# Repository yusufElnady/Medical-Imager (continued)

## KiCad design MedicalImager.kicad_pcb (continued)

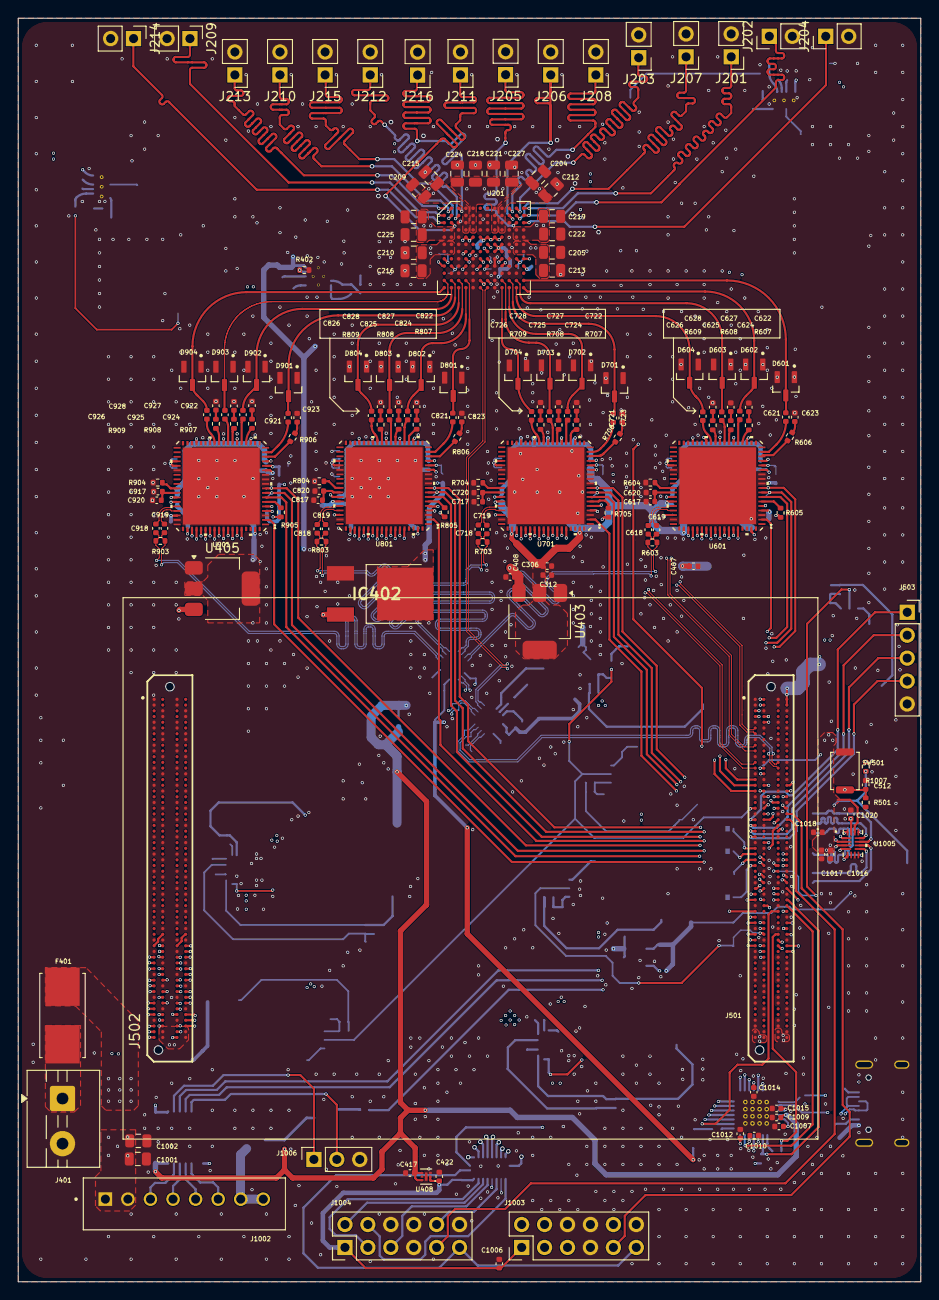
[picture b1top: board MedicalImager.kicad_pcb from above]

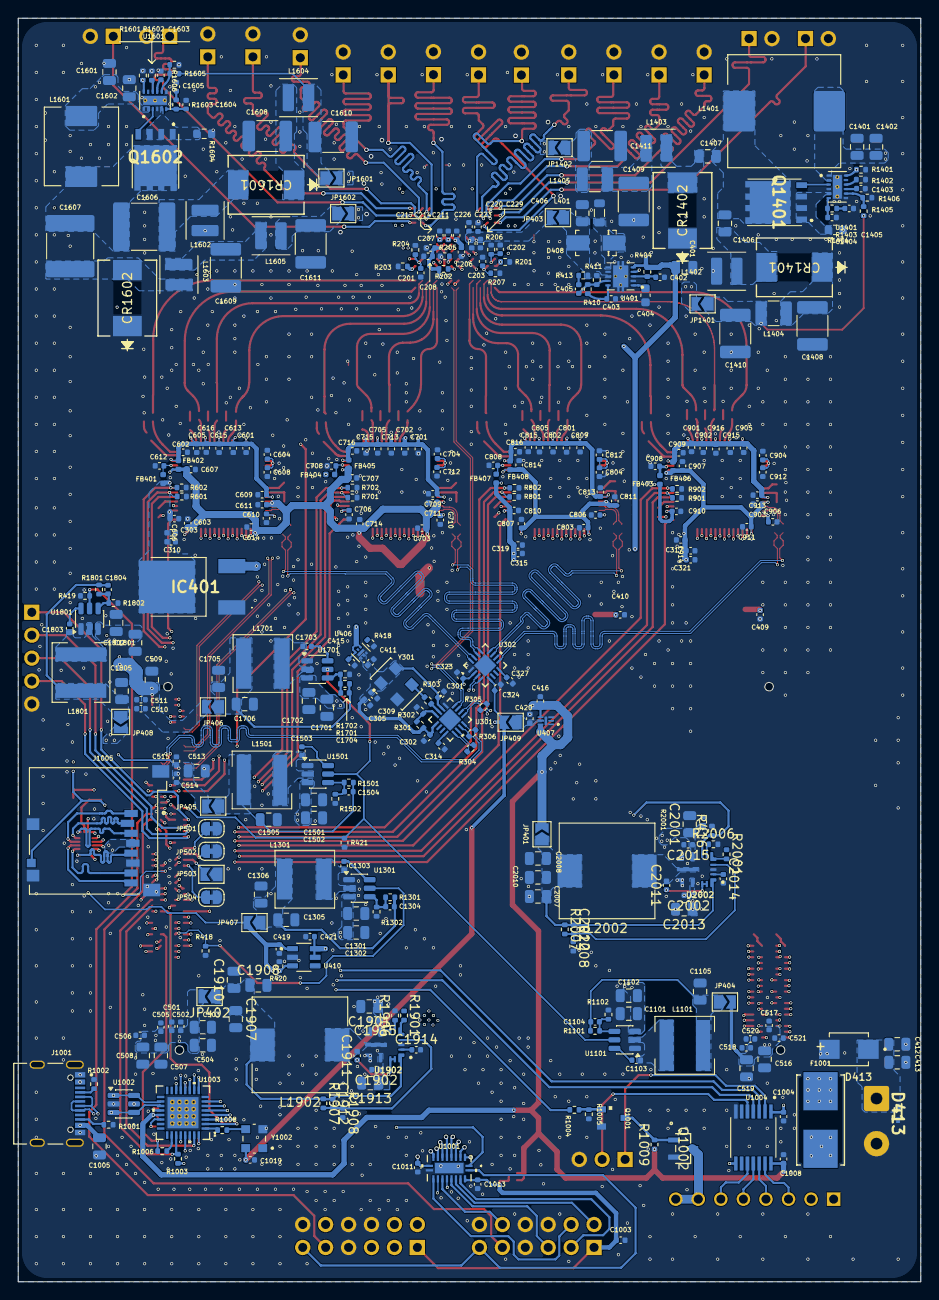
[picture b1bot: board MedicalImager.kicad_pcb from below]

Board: 6 copper layers, 100.0 x 140.0 mm, 519 parts (352 on the bottom side), 394 nets.

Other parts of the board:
D413#2: SMBJ30A; DIOM4336X265N
R418#2: 10K; R_0402_1005Metric
R2001#2: 4K; R_0402_1005Metric

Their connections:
DC_MAIN: R2001#2.1; also elsewhere on the board
DC_MAIN_PRE: D413#2.C; also elsewhere on the board
GND: D413#2.A, R418#2.2; also elsewhere on the board

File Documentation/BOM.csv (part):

Reference;Value;Footprint;Description
C201,C202,C203;1nF;Capacitor_SMD:C_0402_1005Metric;1nF 0402
C204,C205,C209,C210,C212,C213,C215,C216,C218,C219,C221,C222,C224,C225,C227,C228;100nF 200V;Capacitor_SMD:C_0805_2012Metric;100nF 200V 0805
C206,C207,C208,C211,C214,C217,C220,C223,C226,C229,C302,C305,C314,C324,C327,C402,C501,C505,C510,C511,C512,C514,C515,C517,C518,C520,C521,C601,C602,C603,C604,C605,C606,C607,C608,C609,C610,C611,C612,C613,C614,C615,C616,C618,C619,C620,C621,C622,C623,C624,C625,C626,C627,C628,C701,C702,C703,C704,C705,C706,C707,C708,C709,C710,C711,C712,C713,C714,C715,C716,C718,C719,C720,C721,C722,C723,C724,C725,C726,C727,C728,C801,C802,C803,C804,C805,C806,C807,C808,C809,C810,C811,C812,C813,C814,C815,C816,C818,C819,C820,C821,C822,C823,C824,C825,C826,C827,C828,C901,C902,C903,C904,C905,C906,C907,C908,C909,C910,C911,C912,C913,C914,C915,C916,C918,C919,C920,C921,C922,C923,C924,C925,C926,C927,C928,C1004,C1007,C1008,C1009,C1010,C1012,C1017,C1018,C1019,C1020,C1103,C1303,C1403,C1503,C1603,C1703,C1803,C1904,C1906,C2004,C2006;100nF;Capacitor_SMD:C_0402_1005Metric;100nF 0402,100nF 50v 0402
C301,C309,C323;10uF;Capacitor_SMD:C_0402_1005Metric;10uF 0402
C303,C306,C310,C312,C315,C317,C319,C321,C407,C408,C409,C410,C411,C415,C416,C417,C419,C420,C421,C422,C502,C506,C617,C717,C817,C917,C1003,C1006,C1011,C1013,C1016,C1905,C2005;1uF;Capacitor_SMD:C_0402_1005Metric;1uF 0402
C401,C412,C413,C1101,C1102,C1301,C1302,C1401,C1402,C1501,C1502,C1601,C1602,C1701,C1702,C1801,C1802;10uF;Capacitor_SMD:C_0805_2012Metric;10uF 0805 50V,10uF >10v 0805
C403;220nF;Capacitor_SMD:C_0402_1005Metric;220nF 0402
C404;4.7nF;Capacitor_SMD:C_0603_1608Metric;4.7nF 50v 0805
C405;10pF;Capacitor_SMD:C_0402_1005Metric;10pF 0402
C406;22uF;Capacitor_SMD:C_0805_2012Metric;22uF >10v 0805
C503,C504,C507,C508,C1001,C1005,C1907,C1908,C1910,C2007,C2008,C2010;47uF;Capacitor_SMD:C_0805_2012Metric;47uF 0805 10V
C509,C513,C516,C519,C1901,C1902,C1903,C2001,C2002,C2003;4.7uF;Capacitor_SMD:C_0805_2012Metric;4.7uF 0805 >50V
C1002;100nF;Capacitor_SMD:C_0805_2012Metric;100nF 0402
C1014,C1015;4.7uF;Capacitor_SMD:C_0402_1005Metric;4.7uF 0402
C1104,C1504,C1804;56pF;Capacitor_SMD:C_0402_1005Metric;56pF 0402
C1105,C1305,C1306,C1505,C1705,C1706,C1805;100uF;Capacitor_SMD:C_0805_2012Metric;100uF 0805 6.3V
C1304,C1704;47pF;Capacitor_SMD:C_0402_1005Metric;47pF 0402
C1404,C1605;47nF;Capacitor_SMD:C_0402_1005Metric;47nF 0402
C1405;300nF;Capacitor_SMD:C_0402_1005Metric;300nF 0402
C1406;2.2uF 100V;Capacitor_SMD:C_0805_2012Metric;2.2uF 0805 100V
C1407;2.2uF 100v;Capacitor_SMD:C_0805_2012Metric;2.2uF 0805 250V
C1408,C1409,C1410,C1411,C1608,C1609,C1610,C1611;1uF 250V;Capacitor_SMD:C_1812_4532Metric;1uF 250V 1812 - NC1812B105K251CEMN
C1604;8.2nF;Capacitor_SMD:C_0402_1005Metric;8.2nF 0402
C1606,C1607;3.3uF;Capacitor_SMD:C_2220_5750Metric;3.3uF 2220 250V
C1909,C2009;22pF;Capacitor_SMD:C_0402_1005Metric;22pF 0402
D401,D402,D403,D404,D405,D406,D407,D409,D410,D411;LED;LED_SMD:LED_0603_1608Metric;Light emitting diode
D408;B240A-13-F;digikey-footprints:DO-214AC;DIODE SCHOTTKY 40V 2A SMA
D601,D602,D603,D604,D701,D702,D703,D704,D801,D802,D803,D804,D901,D902,D903,D904;MMBD4148SE;MMBD4148SE:SOT95P237X112-3N;SOT-23, 100V, 0.2A, Switching Diode
D1401,D1402,D1601,D1602;S5MB;S5MB:DIOM4336X265N;5A, 1000V, Standard Rectifier
F401;0154007.DRT;0154007.DRT:FUSE_0154007.DRT;7 A 72 V AC 60 V DC Fuse Board Mount (Cartridge Style Excluded) Requires Holder, Surface Mount 2-SMD, Square End Block with Holder
F1001;0154.500DRT;0154-500DRT:0154Series_LTF;
FB401,FB402,FB403,FB404,FB405,FB406,FB407,FB408;BLM15AG601SN1D;Inductor_SMD:L_0402_1005Metric;BLM15AG601SN1D 0402
J201,J202,J203,J204,J205,J206,J207,J208,J209,J210,J211,J212,J213,J214,J215,J216;U.FL-R-SMT-1_80_;U.FL-R-SMT-1_80_:HIROSE_U.FL-R-SMT-1_80_;U.FL (UMCC) Connector Receptacle, Male Pin 50 Ohms Surface Mount Solder
J401;Input Power;TerminalBlock:TerminalBlock_MaiXu_MX126-5.0-02P_1x02_P5.00mm;Generic screw terminal, single row, 01x02, script generated (kicad-library-utils/schlib/autogen/connector/)
J501,J502;REF-226081-01;REF-226081-01:SAMTEC_REF-226081-01;CUSTOM PART OF ADM6-60-01.5-L-4-2-A-TR
J503;JTAG Header;Connector_PinSocket_2.54mm:PinSocket_1x05_P2.54mm_Vertical;Generic connector, single row, 01x05, script generated
J1001;TYPE-C-31-M-12;TYPE-C-31-M-12:HRO_TYPE-C-31-M-12;USB Connectors 24 Receptacle 1 8.94*7.3mm RoHS
J1002;B8B-XH-A;B8B-XH-A:JST_B8B-XH-A;Connector Header Through Hole 8 position 0.098 (2.50mm)
J1003;External Board 1;Connector_PinHeader_2.54mm:PinHeader_2x06_P2.54mm_Vertical;Generic connector, double row, 02x06, counter clockwise pin numbering scheme (similar to DIP package numbering), script generated (kicad-library-utils/schlib/autogen/connector/)
J1004;External Board 2;Connector_PinHeader_2.54mm:PinHeader_2x06_P2.54mm_Vertical;Generic connector, double row, 02x06, counter clockwise pin numbering scheme (similar to DIP package numbering), script generated (kicad-library-utils/schlib/autogen/connector/)
J1005;47352-1001;47352-1001:MOLEX_47352-1001;8 (6 + 2) Position Card Connector Secure Digital - microSD™ Surface Mount, Right Angle Gold
J1006;LCD AUX UART HEADER;Connector_PinSocket_2.54mm:PinSocket_1x03_P2.54mm_Vertical;Generic connector, single row, 01x03, script generated
L401;4.7uH;Inductor_SMD:L_0805_2012Metric;4.7uH 0805 (MLZ2012N4R7LT000)
L1101,L1501,L1801;6.8uH;Inductor_SMD:L_6.3x6.3_H3;6.8uH 6.4*6.3mm - APH0660C-6R8M-TCD5
L1301,L1701;4.7uH;Inductor_SMD:L_6.3x6.3_H3;4.7uH 6*6mm - HPC6045NF-4R7MTH
L1401;150uH;Inductor_SMD:L_SXN_SMDRI127;150uH - PSPMAA1265H-151M-IGP
L1402,L1403;150uH;Inductor_SMD:L_Cenker_CKCS4018;150uH 3.5*3mm - CMLF0302-151MTT
L1404,L1405;68uH;Inductor_SMD:L_1210_3225Metric;68uH 1210 - BCL322520RT-680M-D
L1601;68uH;Inductor_SMD:L_Panasonic_PCC-M0854M;68uH - SMMS0865-680MT
L1602,L1603,L1604,L1605;68uH;Inductor_SMD:L_Cenker_CKCS4018;68uH - CMLF0302-680MTT
L1901,L2001;1uH;Inductor_SMD:L_10.4x10.4_H4.8;1uH 11*10mm - POHS1004-1R0M
Q1001;SI2302DS;SI2302DS:SOT23-3_TO-236AB;N-Channel 20V 2.5A (Tc) 830mW (Tc) Surface Mount TO-236AB (SOT23)
Q1401,Q1601;FDMC86240;FDMC86240:FDMC86139P;Max rDS(on) = 51 m at VGS = 10 V, ID = 4.6 A ; Low Profile - 1 mm max in Power 33 ; Shielded Gate MOSFET Technology; RoHS Compliant ; 100% UIL Tested ; Max rDS(on) = 70 m at VGS = 6 V, ID = 3.9 A
R201,R203,R204,R206,R207,R402,R416,R417,R418,R419,R420,R421,R501,R601,R602,R604,R701,R702,R704,R801,R802,R804,R901,R902,R904,R1003,R1005;10K;Resistor_SMD:R_0402_1005Metric;10K 0402
R301,R302,R605,R705,R805,R905,R1004,R1406,R1606,R1902,R2002;1K;Resistor_SMD:R_0402_1005Metric;1K 0402
R303,R1006,R1008;50R;Resistor_SMD:R_0402_1005Metric;50R 0402
R304,R305,R306,R603,R703,R803,R903;100R;Resistor_SMD:R_0402_1005Metric;100R 0402
R401;1K;Resistor_SMD:R_0402_1005Metric;1K 0402
R403,R405;0.5K;Resistor_SMD:R_0402_1005Metric;0.5K 0402
R404;10R;Resistor_SMD:R_0402_1005Metric;10R 0402
R406,R407,R408,R409;330R;Resistor_SMD:R_0402_1005Metric;330R 0402
R410;150K;Resistor_SMD:R_0402_1005Metric;150K 0402
R411;619K;Resistor_SMD:R_0402_1005Metric;619K 0402
R412,R414,R415;220R;Resistor_SMD:R_0402_1005Metric;220R 0402
R413,R1007,R1101,R1301,R1401,R1501,R1601,R1605,R1701,R1801,R1903,R2003;100K;Resistor_SMD:R_0402_1005Metric;100K 0402
R606,R607,R608,R609,R706,R707,R708,R709,R806,R807,R808,R809,R906,R907,R908,R909;8R;Resistor_SMD:R_0402_1005Metric;8R 0402
R1001,R1002;5.1K;Resistor_SMD:R_0402_1005Metric;5.1K 0402
R1102,R1502,R1802;22K;Resistor_SMD:R_0402_1005Metric;22K 0402
R1302,R1405,R1702;49.9K;Resistor_SMD:R_0402_1005Metric;49.9K 0402
R1402,R1602;150k;Resistor_SMD:R_0402_1005Metric;150k 0402
R1403;570R;Resistor_SMD:R_0402_1005Metric;570R 0402
R1404,R1604;10mOhm;Resistor_SMD:R_0603_1608Metric;10mOhm 0603
R1603;3.3k;Resistor_SMD:R_0402_1005Metric;3.3k 0402
R1901,R2001;4K;Resistor_SMD:R_0402_1005Metric;4K 0402
R1904,R2004;147K;Resistor_SMD:R_0402_1005Metric;147K 0402
R1905,R2005;20K;Resistor_SMD:R_0402_1005Metric;20K 0402
SW501;RESET;Button_Switch_SMD:SW_Push_SPST_NO_Alps_SKRK;Push button switch, generic, two pins
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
